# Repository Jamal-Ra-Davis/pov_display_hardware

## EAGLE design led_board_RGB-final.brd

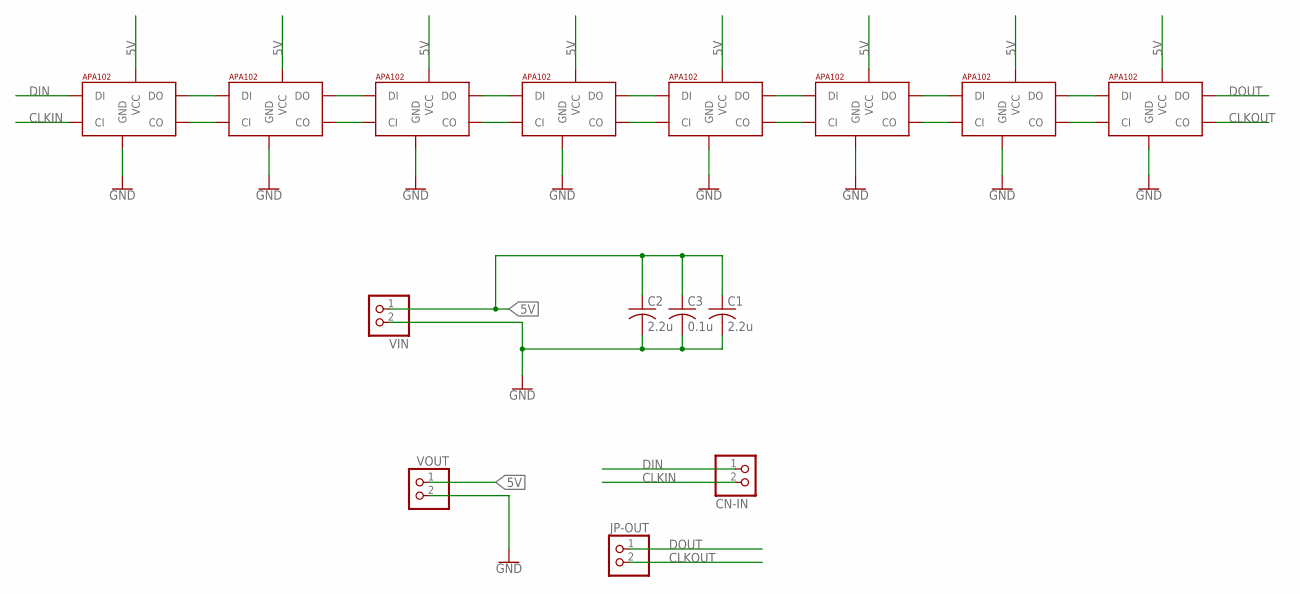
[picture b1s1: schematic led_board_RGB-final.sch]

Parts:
C1, C2: 2.2u; C1206
C3: 0.1u; C0805
CN-IN: JST_2PIN-THM-RA; JST-PH-2-THM-RA
JP-OUT: PINHD-1X2; 1X02
U$1, U$2, U$3, U$4, U$5, U$6, U$7, U$8: APA1022020; APA102_2020
VIN: JST_2PIN-THM-RA; JST-PH-2-THM-RA
VOUT: PINHD-1X2; 1X02

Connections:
5V: C1.1, C2.1, C3.1, U$1.V_CC (VCC), U$2.V_CC (VCC), U$3.V_CC (VCC), U$4.V_CC (VCC), U$5.V_CC (VCC), U$6.V_CC (VCC), U$7.V_CC (VCC), U$8.V_CC (VCC), VIN.1 (2), VOUT.1
CLKIN: CN-IN.2 (1), U$1.C_IN (CI)
CLKOUT: JP-OUT.2, U$8.CL_OUT (CO)
DIN: CN-IN.1 (2), U$1.D_IN (DI)
DOUT: JP-OUT.1, U$8.D_OUT (DO)
GND: C1.2, C2.2, C3.2, U$1.GND, U$2.GND, U$3.GND, U$4.GND, U$5.GND, U$6.GND, U$7.GND, U$8.GND, VIN.2 (1), VOUT.2
unnamed: U$1.D_OUT (DO), U$2.D_IN (DI)
unnamed: U$1.CL_OUT (CO), U$2.C_IN (CI)
unnamed: U$2.D_OUT (DO), U$3.D_IN (DI)
unnamed: U$2.CL_OUT (CO), U$3.C_IN (CI)
unnamed: U$3.D_OUT (DO), U$4.D_IN (DI)
unnamed: U$3.CL_OUT (CO), U$4.C_IN (CI)
unnamed: U$4.D_OUT (DO), U$5.D_IN (DI)
unnamed: U$4.CL_OUT (CO), U$5.C_IN (CI)
unnamed: U$5.D_OUT (DO), U$6.D_IN (DI)
unnamed: U$5.CL_OUT (CO), U$6.C_IN (CI)
unnamed: U$6.D_OUT (DO), U$7.D_IN (DI)
unnamed: U$6.CL_OUT (CO), U$7.C_IN (CI)
unnamed: U$7.D_OUT (DO), U$8.D_IN (DI)
unnamed: U$7.CL_OUT (CO), U$8.C_IN (CI)

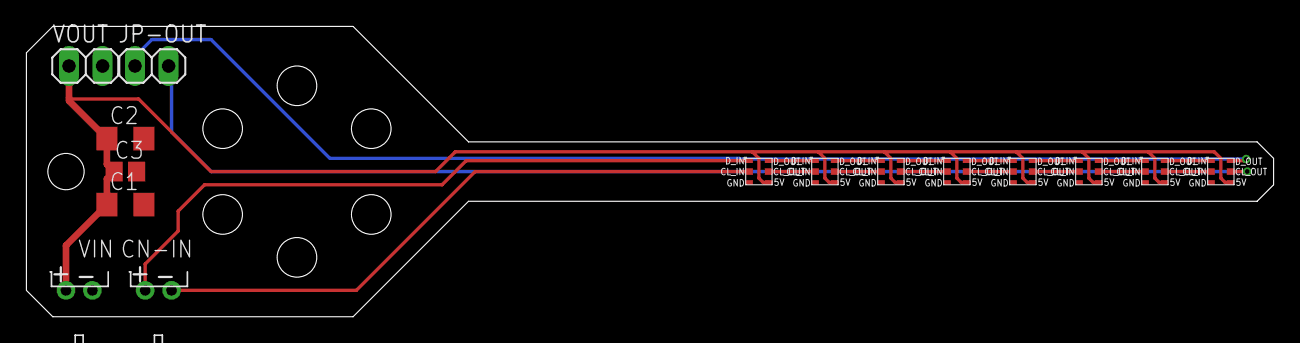
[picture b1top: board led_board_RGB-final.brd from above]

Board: 2 copper layers, 94.5 x 22.0 mm, 15 parts (0 on the bottom side), 20 nets.

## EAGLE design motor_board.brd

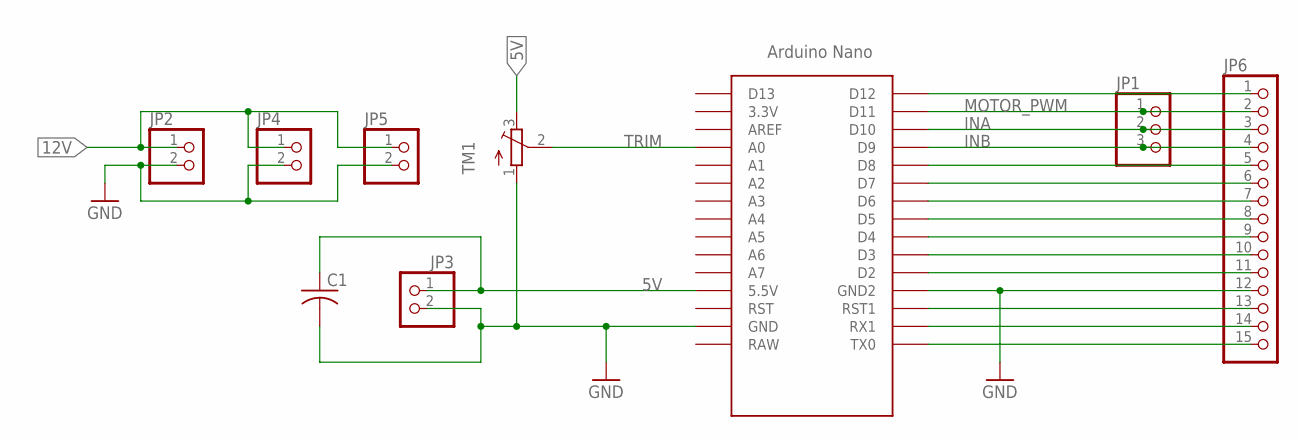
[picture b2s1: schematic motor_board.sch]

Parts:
C1: C-US025-060X050; C025-060X050
JP1: PINHD-1X3; 1X03
JP2, JP3, JP4, JP5: PINHD-1X2; 1X02
JP6: PINHD-1X15; 1X15
TM1: TRIMPOT3386; TRIM-3386
U$2: NANO

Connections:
5V: C1.1, JP3.1, TM1.3 (E), U$2.5V (5.5V)
12V: JP2.1, JP4.1, JP5.1
GND: C1.2, JP2.2, JP3.2, JP4.2, JP5.2, JP6.12, TM1.1 (A), U$2.GND, U$2.GND1 (GND2)
INA: JP1.2, JP6.3, U$2.D10
INB: JP1.3, JP6.4, U$2.D9
MOTOR_PWM: JP1.1, JP6.2, U$2.D11
unnamed: JP6.1, U$2.D12
unnamed: JP6.5, U$2.D8
unnamed: JP6.6, U$2.D7
unnamed: JP6.7, U$2.D6
unnamed: JP6.8, U$2.D5
unnamed: JP6.9, U$2.D4
unnamed: JP6.10, U$2.D3
unnamed: JP6.11, U$2.D2
unnamed: JP6.13, U$2.RST1
unnamed: JP6.14, U$2.RX1
unnamed: JP6.15, U$2.TX0
TRIM: TM1.2 (S), U$2.A0

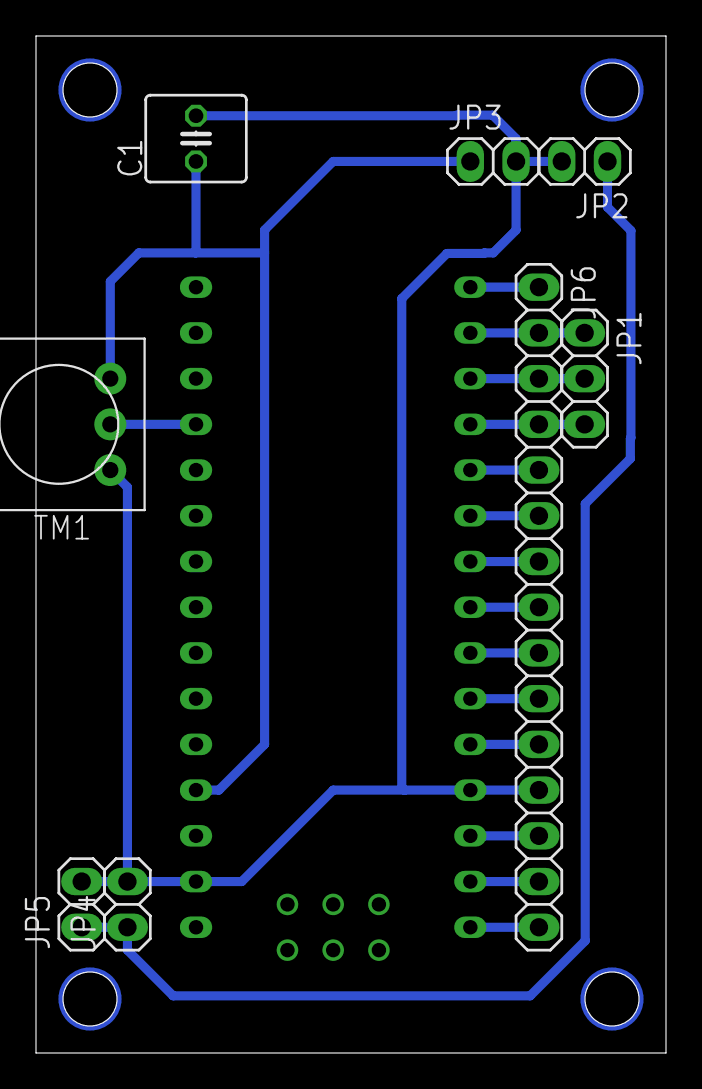
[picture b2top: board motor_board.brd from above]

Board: 2 copper layers, 35.0 x 56.5 mm, 9 parts (0 on the bottom side), 18 nets.

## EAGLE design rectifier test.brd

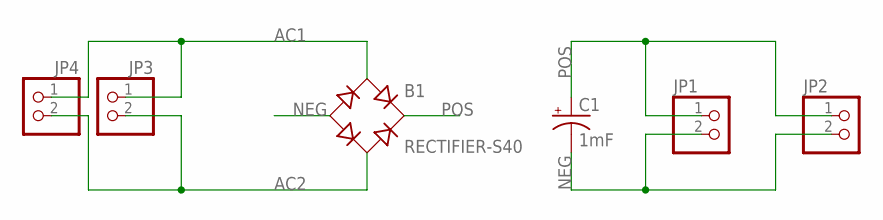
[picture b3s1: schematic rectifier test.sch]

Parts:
B1: RECTIFIER-S40; TO-269AA
C1: 1mF; CPOL-RADIAL-5MM-10MM
JP1, JP2, JP3, JP4: PINHD-1X2; 1X02

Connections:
AC1: B1.AC1, JP3.1, JP4.1
AC2: B1.AC2, JP3.2, JP4.2
NEG: B1.-, C1.-, JP1.2, JP2.2
POS: B1.+, C1.+, JP1.1, JP2.1

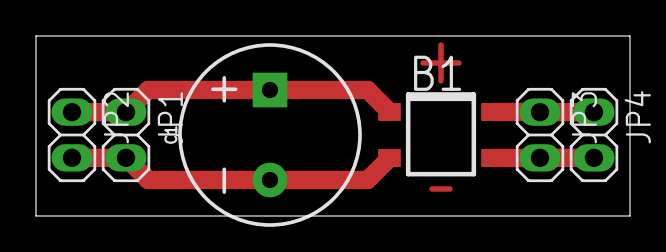
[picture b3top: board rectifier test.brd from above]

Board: 2 copper layers, 33.0 x 10.0 mm, 6 parts (0 on the bottom side), 4 nets.

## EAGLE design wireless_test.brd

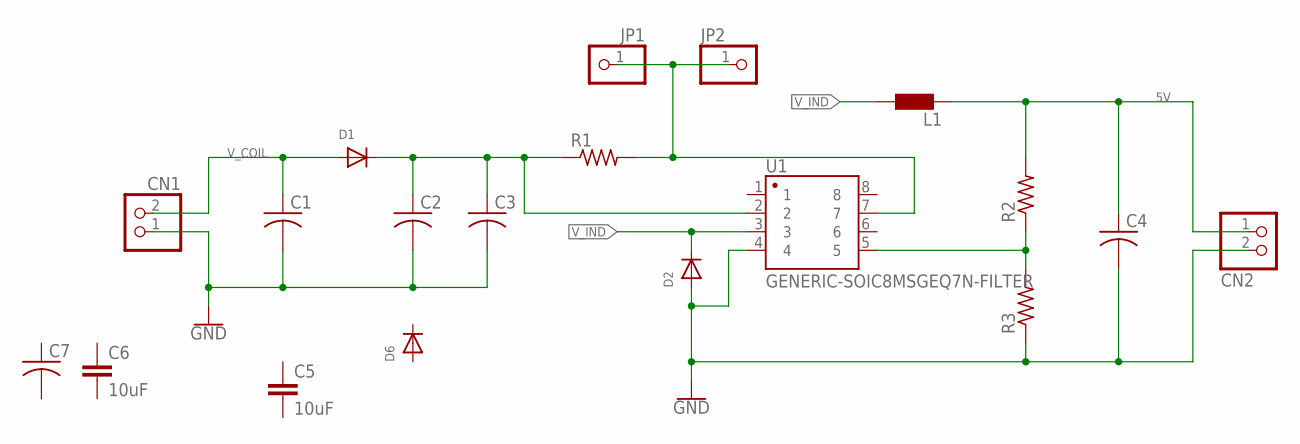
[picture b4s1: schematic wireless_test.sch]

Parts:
C1, C2, C3, C4: C-USC0805; C0805
C5: 10uF; 0805
C6: 10uF; 1206
C7: C-USC1206; C1206
CN1, CN2: JST_2PIN-THM-RA; JST-PH-2-THM-RA
D1: DIODESMA; SMADIODE
D2: DIODESOD-523; SOD-523
D6: DIODE_SOD-123FL; SOD-123FL
JP1, JP2: PINHD-1X1; 1X01
L1: LL3230M; L3230M
R1, R2, R3: R-US_R0603; R0603
U1: GENERIC-SOIC8MSGEQ7N-FILTER; SO08

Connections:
5V: C4.1, CN2.1 (2), L1.2, R2.2
GND: C1.2, C2.2, C3.2, C4.2, CN1.1 (2), CN2.2 (1), D2.A, R3.1, U1.4
unnamed: R2.1, R3.2, U1.5
unnamed: C2.1, C3.1, D1.C, R1.1, U1.2
unnamed: JP1.1, JP2.1, R1.2, U1.7
V_COIL: C1.1, CN1.2 (1), D1.A
V_IND: D2.K (C), L1.1, U1.3

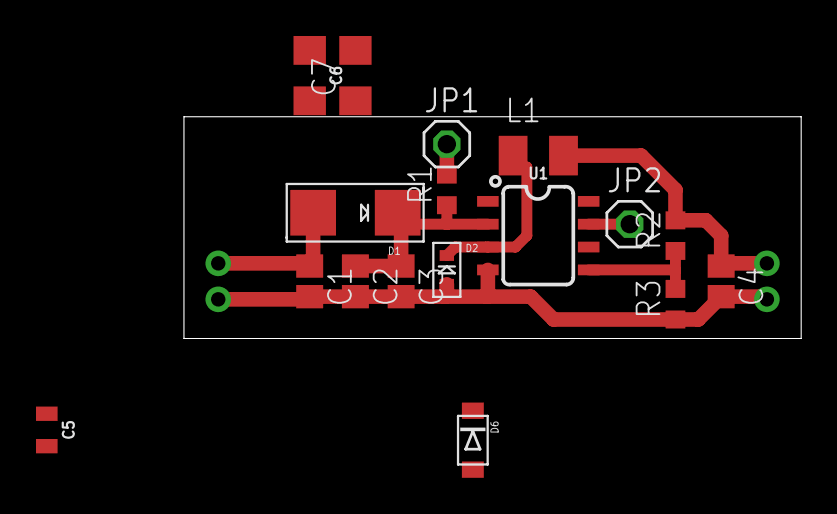
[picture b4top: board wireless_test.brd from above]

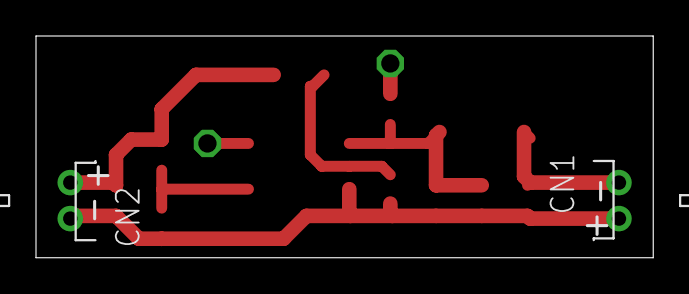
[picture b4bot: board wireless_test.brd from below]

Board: 2 copper layers, 34.3 x 12.3 mm, 19 parts (2 on the bottom side), 7 nets.

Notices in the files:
parts and their libraries:
SparkFun-PowerSymbols: Licensing: Creative Commons ShareAlike 4.0 International - https://creativecommons.org/licenses/by-sa/4.0
